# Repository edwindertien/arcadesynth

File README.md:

# arcadesynth
## intro
in this repository the design files of the arcade modular synth. 

The case started out as a laptop based arcade machine, but was converted to a modular rack with three sections. A gui (user interface) module has been designed to link arcade inputs (joysticks, switches) to analogue (0-5V) outputs to control other synth modules.

## design
### case

Files for the case design have been added. This is one big (cluttered) *.svg drawing and a picture for reference.
### gui
The pcb (electronics) and arduino firmware for a gui module linking 16 inputs (switches, analogue potentiometers etc) to 8 outputs (triggers, modulation, cv (pitch), LFO)
### furby

The fabulously furry synthesiser module designed for [FabAcademy 2024](https://fabacademy.org/2024/labs/waag/students/edwin-dertien/project/). Containing 3D print files for a small animatronic furby face, PCB (kicad) and software for RPi PICO

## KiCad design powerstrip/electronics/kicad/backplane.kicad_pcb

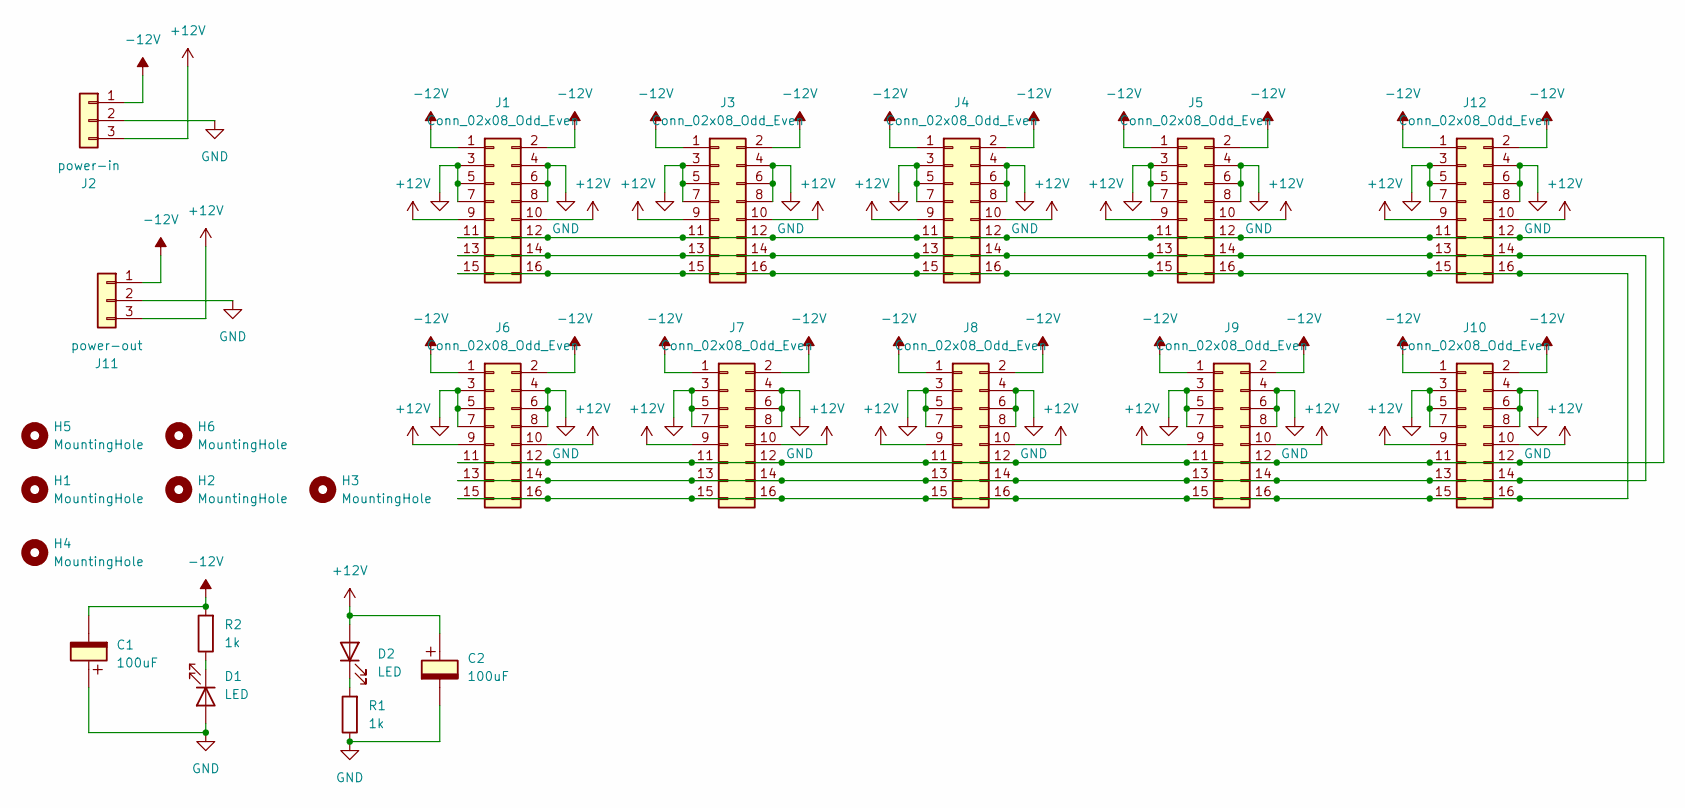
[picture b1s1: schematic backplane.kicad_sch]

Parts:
C1, C2: 100uF; CP_Radial_D6.3mm_P2.50mm
D1, D2: LED; LED_D3.0mm
H1, H2, H3, H4, H5, H6: MountingHole; MountingHole_3.2mm_M3
J1, J3, J4, J5, J6, J7, J8, J9, J10, J12: Conn_02x08_Odd_Even; IDC-Header_2x08_P2.54mm_Vertical
J2: power-in; Molex_KK-396_5273-03A_1x03_P3.96mm_Vertical
J11: power-out; Molex_KK-396_5273-03A_1x03_P3.96mm_Vertical
R1, R2: 1k; R_Axial_DIN0207_L6.3mm_D2.5mm_P7.62mm_Horizontal

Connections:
+12V: C2.1, D2.2 (A), J1.9, J1.10, J2.3, J3.9, J3.10, J4.9, J4.10, J5.9, J5.10, J6.9, J6.10, J7.9, J7.10, J8.9, J8.10, J9.9, J9.10, J10.9, J10.10, J11.3, J12.9, J12.10
-12V: C1.2, J1.1, J1.2, J2.1, J3.1, J3.2, J4.1, J4.2, J5.1, J5.2, J6.1, J6.2, J7.1, J7.2, J8.1, J8.2, J9.1, J9.2, J10.1, J10.2, J11.1, J12.1, J12.2, R2.2
GND: C1.1, C2.2, D1.2 (A), J1.3, J1.4, J1.5, J1.6, J1.7, J1.8, J2.2, J3.3, J3.4, J3.5, J3.6, J3.7, J3.8, J4.3, J4.4, J4.5, J4.6, J4.7, J4.8, J5.3, J5.4, J5.5, J5.6, J5.7, J5.8, J6.3, J6.4, J6.5, J6.6, J6.7, J6.8, J7.3, J7.4, J7.5, J7.6, J7.7, J7.8, J8.3, J8.4, J8.5, J8.6, J8.7, J8.8, J9.3, J9.4, J9.5, J9.6, J9.7, J9.8, J10.3, J10.4, J10.5, J10.6, J10.7, J10.8, J11.2, J12.3, J12.4, J12.5, J12.6, J12.7, J12.8, R1.1
unnamed: D1.1 (K), R2.1
unnamed: D2.1 (K), R1.2
unnamed: J1.11, J1.12, J3.11, J3.12, J4.11, J4.12, J5.11, J5.12, J6.11, J6.12, J7.11, J7.12, J8.11, J8.12, J9.11, J9.12, J10.11, J10.12, J12.11, J12.12
unnamed: J1.13, J1.14, J3.13, J3.14, J4.13, J4.14, J5.13, J5.14, J6.13, J6.14, J7.13, J7.14, J8.13, J8.14, J9.13, J9.14, J10.13, J10.14, J12.13, J12.14
unnamed: J1.15, J1.16, J3.15, J3.16, J4.15, J4.16, J5.15, J5.16, J6.15, J6.16, J7.15, J7.16, J8.15, J8.16, J9.15, J9.16, J10.15, J10.16, J12.15, J12.16

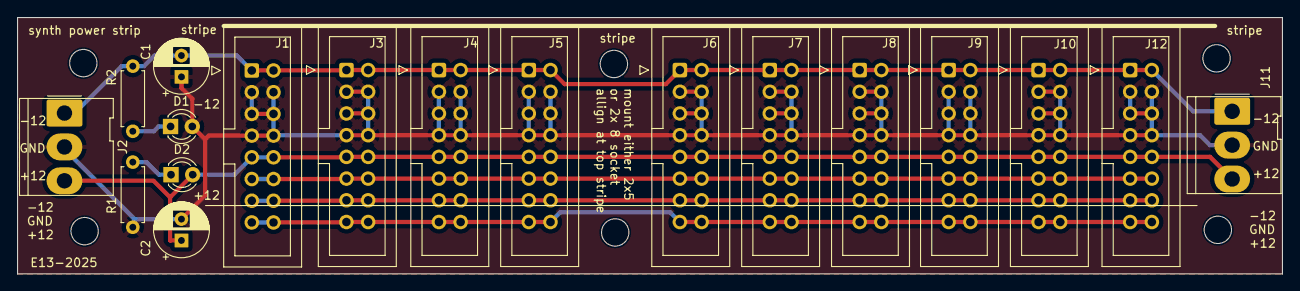
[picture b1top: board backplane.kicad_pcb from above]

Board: 2 copper layers, 148.0 x 30.0 mm, 24 parts (0 on the bottom side), 8 nets.

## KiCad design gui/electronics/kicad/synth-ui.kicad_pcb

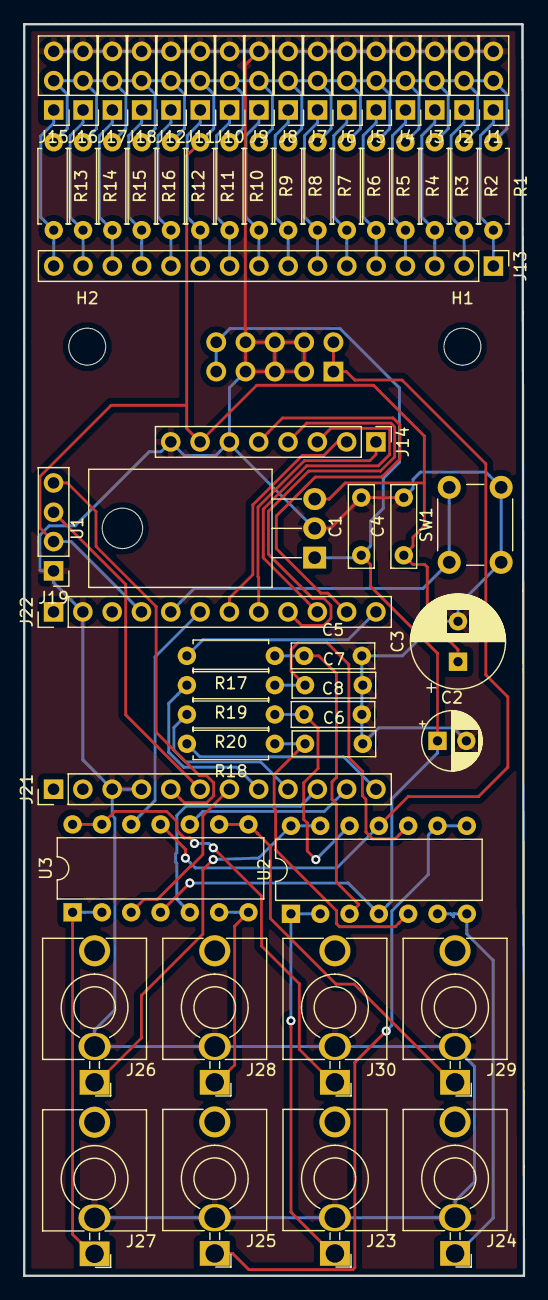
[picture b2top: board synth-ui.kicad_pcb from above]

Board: 2 copper layers, 43.3 x 108.5 mm, 64 parts (1 on the bottom side), 48 nets.

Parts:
C1, C4, C5, C6, C7, C8: 100n; C_Rect_L7.0mm_W2.0mm_P5.00mm
C2: 10uF; CP_Radial_D5.0mm_P2.50mm
C3: 100uF; CP_Radial_D8.0mm_P3.50mm
H1, H2: MountingHole; MountingHole_3.2mm_M3
J1, J2, J3, J4, J5, J6, J7, J8, J9, J10, J11, J12, J15, J16, J17, J18: Conn_01x03; PinHeader_1x03_P2.54mm_Vertical
J13: mux-ports; PinHeader_1x16_P2.54mm_Vertical
J14: mux-sig; PinHeader_1x08_P2.54mm_Vertical
J19: OLED; PinHeader_1x04_P2.54mm_Vertical
J20: Conn_02x05_Odd_Even; IDC-Header_2x05_P2.54mm_Vertical
J21: pro-mini-L; PinHeader_1x12_P2.54mm_Vertical
J22: pro-mini-R; PinHeader_1x12_P2.54mm_Vertical
J23, J24, J25, J26, J27, J28, J29, J30: Conn_01x02; Jack_3.5mm_QingPu_WQP-PJ398SM_Vertical_CircularHoles
R1, R2, R3, R4, R5, R6, R7, R8, R9, R10, R11, R12, R13, R14, R15, R16: 10k; R_Axial_DIN0207_L6.3mm_D2.5mm_P7.62mm_Horizontal
R17, R18, R19, R20: 100k; R_Axial_DIN0207_L6.3mm_D2.5mm_P7.62mm_Horizontal
SW1: SW_Push; SW_PUSH_6mm
U1: LM7805_TO220; TO-220-3_Horizontal_TabDown
U2, U3: TL074; DIP-14_W7.62mm

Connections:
+12V: C1.1, C2.1, J20.9, J20.10, U1.1, U2.4, U3.4
-12V: J20.1, J20.2, U2.11, U3.11
/A0: J14.1, J22.8
/D2: J19.4, J21.5
/D3: J19.3, J21.6
/D4: J21.7, U3.3
/D5: J21.8, R19.2
/D6: J21.9, R20.2
/D7: J21.10, U3.5
/D8: J21.11, U3.10
/D9: J21.12, R18.2
/D10: J22.12, R17.2
/D14: J14.3, J22.10
/D15: J14.4, J22.9
/D16: J14.5, J22.11
/D19: J14.2, J22.7
/D20: J22.6, U3.12
/D21: J22.5, SW1.1
GND: C1.2, C2.2, C3.2, C4.2, C5.2, C6.2, C7.2, C8.2, J1.3, J2.3, J3.3, J4.3, J5.3, J6.3, J7.3, J8.3, J9.3, J10.3, J11.3, J12.3, J14.6, J14.8, J15.3, J16.3, J17.3, J18.3, J19.1, J20.3, J20.4, J20.5, J20.6, J20.7, J20.8, J21.3, J21.4, J22.2, J23.2, J24.2, J25.2, J26.2, J27.2, J28.2, J29.2, J30.2, SW1.2, U1.2
unnamed: C5.1, R17.1, U2.3
unnamed: C6.1, R18.1, U2.5
unnamed: C7.1, R19.1, U2.10
unnamed: C8.1, R20.1, U2.12
unnamed: J1.1, J13.1, R1.2
unnamed: J10.1, J13.10, R10.2
unnamed: J11.1, J13.11, R11.2
unnamed: J12.1, J13.12, R12.2
unnamed: J2.1, J13.2, R2.2
unnamed: J3.1, J13.3, R3.2
unnamed: J4.1, J13.4, R4.2
unnamed: J5.1, J13.5, R5.2
unnamed: J6.1, J13.6, R6.2
unnamed: J7.1, J13.7, R7.2
unnamed: J8.1, J13.8, R8.2
unnamed: J9.1, J13.9, R9.2
unnamed: J13.13, J18.1, R16.2
unnamed: J13.14, J17.1, R15.2
unnamed: J13.15, J16.1, R14.2
unnamed: J13.16, J15.1, R13.2
unnamed: J23.1, U2.1, U2.2
unnamed: J24.1, U2.6, U2.7
unnamed: J25.1, U2.8, U2.9
unnamed: J26.1, U2.13, U2.14
unnamed: J27.1, U3.1, U3.2
unnamed: J28.1, U3.6, U3.7
unnamed: J29.1, U3.8, U3.9
unnamed: J30.1, U3.13, U3.14
VCC: C3.1, C4.1, J1.2, J2.2, J3.2, J4.2, J5.2, J6.2, J7.2, J8.2, J9.2, J10.2, J11.2, J12.2, J14.7, J15.2, J16.2, J17.2, J18.2, J19.2, J22.4, R1.1, R2.1, R3.1, R4.1, R5.1, R6.1, R7.1, R8.1, R9.1, R10.1, R11.1, R12.1, R13.1, R14.1, R15.1, R16.1, U1.3

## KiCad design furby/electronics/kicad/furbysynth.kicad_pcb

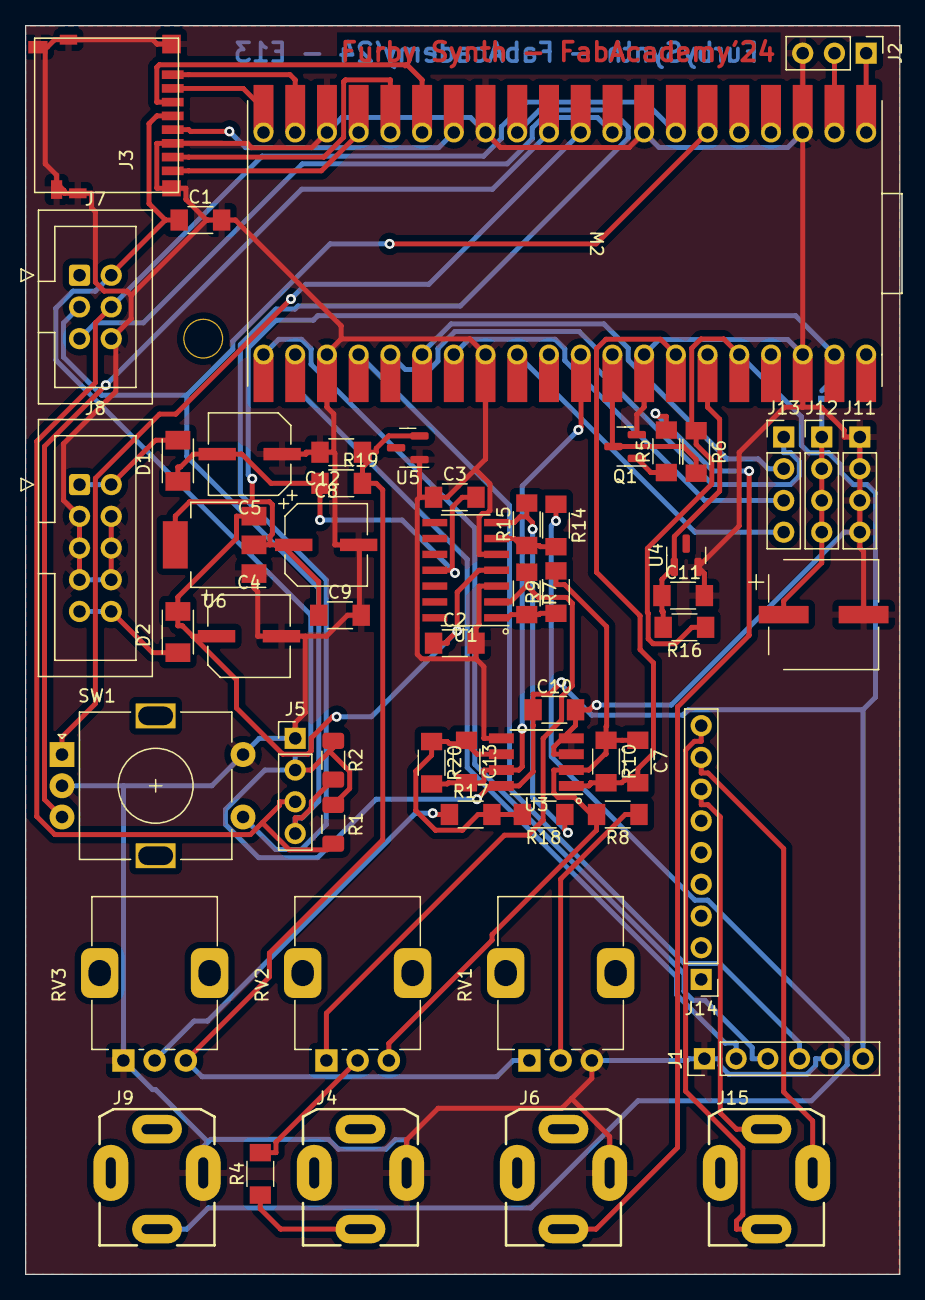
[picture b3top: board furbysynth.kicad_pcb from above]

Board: 2 copper layers, 70.0 x 100.0 mm, 58 parts (1 on the bottom side), 50 nets.

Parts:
C1: 10uF; C_1206
C2, C3, C9, C10, C12: 100n; C_1206
C4, C5: 47uF; CP_Elec_D6.3mm_H6.1mm
C7, C13: 1nF; C_1206
C8: 22uF; CP_Elec_D6.3mm_H6.1mm
C11: 470n; C_1206
C14: 470uF; CP_Elec_D8.0mm
D1, D2: CDBM1100-G; SOD-123T
H1: MountingHole; MountingHole_3mm
J1: PCM5102 audio; PinHeader_1x06_P2.54mm_Vertical
J2: Serial Debug; PinHeader_1x03_P2.54mm_Vertical
J3: Micro_SD_Socket; MicroSD_Amphenol_114-00841-68
J4: mod; Jack_3.5mm_QingPu_WQP-PJ3410_Vertical
J5: OLED - SSD1306; PinHeader_1x04_P2.54mm_Vertical
J6: gate; Jack_3.5mm_QingPu_WQP-PJ3410_Vertical
J7: PCA9685 servo driver; IDC-Header_2x03_P2.54mm_Vertical
J8: Conn_02x05_Odd_Even; IDC-Header_2x05_P2.54mm_Vertical
J9: CV; Jack_3.5mm_QingPu_WQP-PJ3410_Vertical
J11: gmd; PinHeader_1x04_P2.54mm_Vertical
J12: vcc; PinHeader_1x04_P2.54mm_Vertical
J13: sig; PinHeader_1x04_P2.54mm_Vertical
J14: pcm5102 module connector; PinHeader_1x09_P2.54mm_Vertical
J15: audio out; Jack_3.5mm_QingPu_WQP-PJ3410_Vertical
JP1: power; SolderJumper-2_P1.3mm_Bridged_RoundedPad1.0x1.5mm
M2: Pico; RaspberryPi_PicoW_Combined
Q1: MMBT3904; SOT-23
R1, R2: 4k7; R_1206_3216Metric_Pad1.30x1.75mm_HandSolder
R4, R5, R14: 100k; R_1206
R6: 10k; R_1206
R7, R9, R15, R18, R20: 24.9k; R_1206
R8: 200k; R_1206
R10: 49.9k; R_1206
R16: 1k; R_1206
R17: 120k; R_1206
R19: R; R_1206
RV1, RV2, RV3: 10k; Potentiometer_Alps_RK09K_Single_Vertical
SW1: RotaryEncoder_Switch; RotaryEncoder_Alps_EC11E-Switch_Vertical_H20mm
U1: LM324; SOIC-14_3.9x8.7mm_P1.27mm
U3: TLC272; SOIC-8_3.9x4.9mm_P1.27mm
U4: LM4040DBZ-2.5; SOT-23
U5: LM4040DBZ-10; SOT-23
U6: LM1117MP-5.0; SOT-223-3_TabPin2

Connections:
+3.3V: C1.1, C10.1, J1.6, J3.4 (VDD), J5.2, J7.2, M2.36 (3V3_OUT), R1.1, R2.1, R6.1, R16.1, U3.8 (V+)
+5V: C8.1, C9.1, JP1.1 (A), M2.39 (VSYS), U6.2 (VO)
+12V: C2.1, C4.1, D2.1 (K), U1.4 (V+), U6.3 (VI)
-12V: C3.2, C5.2, D1.2 (A), R19.1, U1.11 (V-)
/AREF: C11.1, M2.35 (ADC_VREF), R16.2, U4.1 (K)
/BCK: J1.2, M2.22 (GP17)
/CV: C13.2, M2.31 (GP26), R20.2, U3.7
/DIN: J1.3, M2.21 (GP16)
/EN: J7.5, M2.9 (GP6)
/GATE: M2.32 (GP27), Q1.3 (C), R6.2
/GP4: J5.4, J7.3, M2.6 (GP4), R2.2
/GP5: J5.3, J7.4, M2.7 (GP5), R1.2
/GP7: M2.10 (GP7), SW1.A
/GP8: M2.11 (GP8), SW1.B
/GP9: M2.12 (GP9), SW1.S1
/GP10: J3.5 (CLK), M2.14 (GP10)
/GP11: J3.3 (CMD), M2.15 (GP11)
/GP12: J3.7 (DAT0), M2.16 (GP12)
/GP13: J3.8 (DAT1), M2.17 (GP13)
/GP14: J3.1 (DAT2), M2.19 (GP14)
/GP15: J3.2 (DAT3/CD), M2.20 (GP15)
/GP18: J1.4, M2.24 (GP18)
/GP19: J13.1, M2.25 (GP19)
/GP20: J13.2, M2.26 (GP20)
/GP21: J13.3, M2.27 (GP21)
/GP22: J13.4, M2.29 (GP22)
/MOD: C7.2, M2.34 (GP28), R10.2, U3.1
/RX0: J2.2, M2.2 (GP1)
/TX0: J2.1, M2.1 (GP0)
/ref-10: C12.1, R19.2, RV1.1, RV3.3, U5.2 (A)
GND: C1.2, C2.2, C3.1, C4.2, C5.1, C8.2, C9.2, C10.2, C11.2, C12.2, C14.2, J1.1, J1.5, J2.3, J3.6 (VSS), J3.9 (SHIELD), J4.S, J5.1, J6.S, J7.6, J8.3, J8.4, J8.5, J8.6, J8.7, J8.8, J9.S, J11.1, J11.2, J11.3, J11.4, M2.3 (GND), M2.8 (GND), M2.13 (GND), M2.18 (GND), M2.23 (GND), M2.28 (GND), M2.33 (GND), M2.38 (GND), Q1.2 (E), RV1.3, RV3.1, SW1.C, SW1.S2, U1.3 (+), U1.5 (+), U3.3 (+), U3.4 (V-), U3.5 (+), U4.2 (A), U5.1 (K), U6.1 (GND)
unnamed: D1.1 (K), J8.1, J8.2
unnamed: D2.2 (A), J8.9, J8.10
unnamed: J4.T, R4.1
unnamed: J6.T, R5.2
unnamed: J9.T, R14.1
unnamed: C14.1, J12.1, J12.2, J12.3, J12.4, JP1.2 (B)
unnamed: J14.7, J15.R
unnamed: J14.8, J15.S
unnamed: J14.9, J15.T
unnamed: Q1.1 (B), R5.1
unnamed: R4.2, RV2.2
unnamed: R7.2, R9.1, U1.1
unnamed: R8.1, RV1.2
unnamed: R15.2, R18.1, U1.7
unnamed: R17.1, RV3.2
unnamed: R7.1, RV2.1, U1.2 (-)
unnamed: R14.2, R15.1, U1.6 (-)
unnamed: C7.1, R8.2, R9.2, R10.1, RV2.3, U3.2 (-)
unnamed: C13.1, R17.2, R18.2, R20.1, U3.6 (-)

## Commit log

2024-07-12 first commit with design files
2024-07-13 image
2024-07-13 another image
2025-04-11 added files for powerstrip design
2025-04-11 furby is back
2025-06-30 (update with kicad files that should probably have been in the gitignore)
